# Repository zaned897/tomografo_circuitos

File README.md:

# tomografo_circuitos
todos los circuitos del tomografo fotoacustico

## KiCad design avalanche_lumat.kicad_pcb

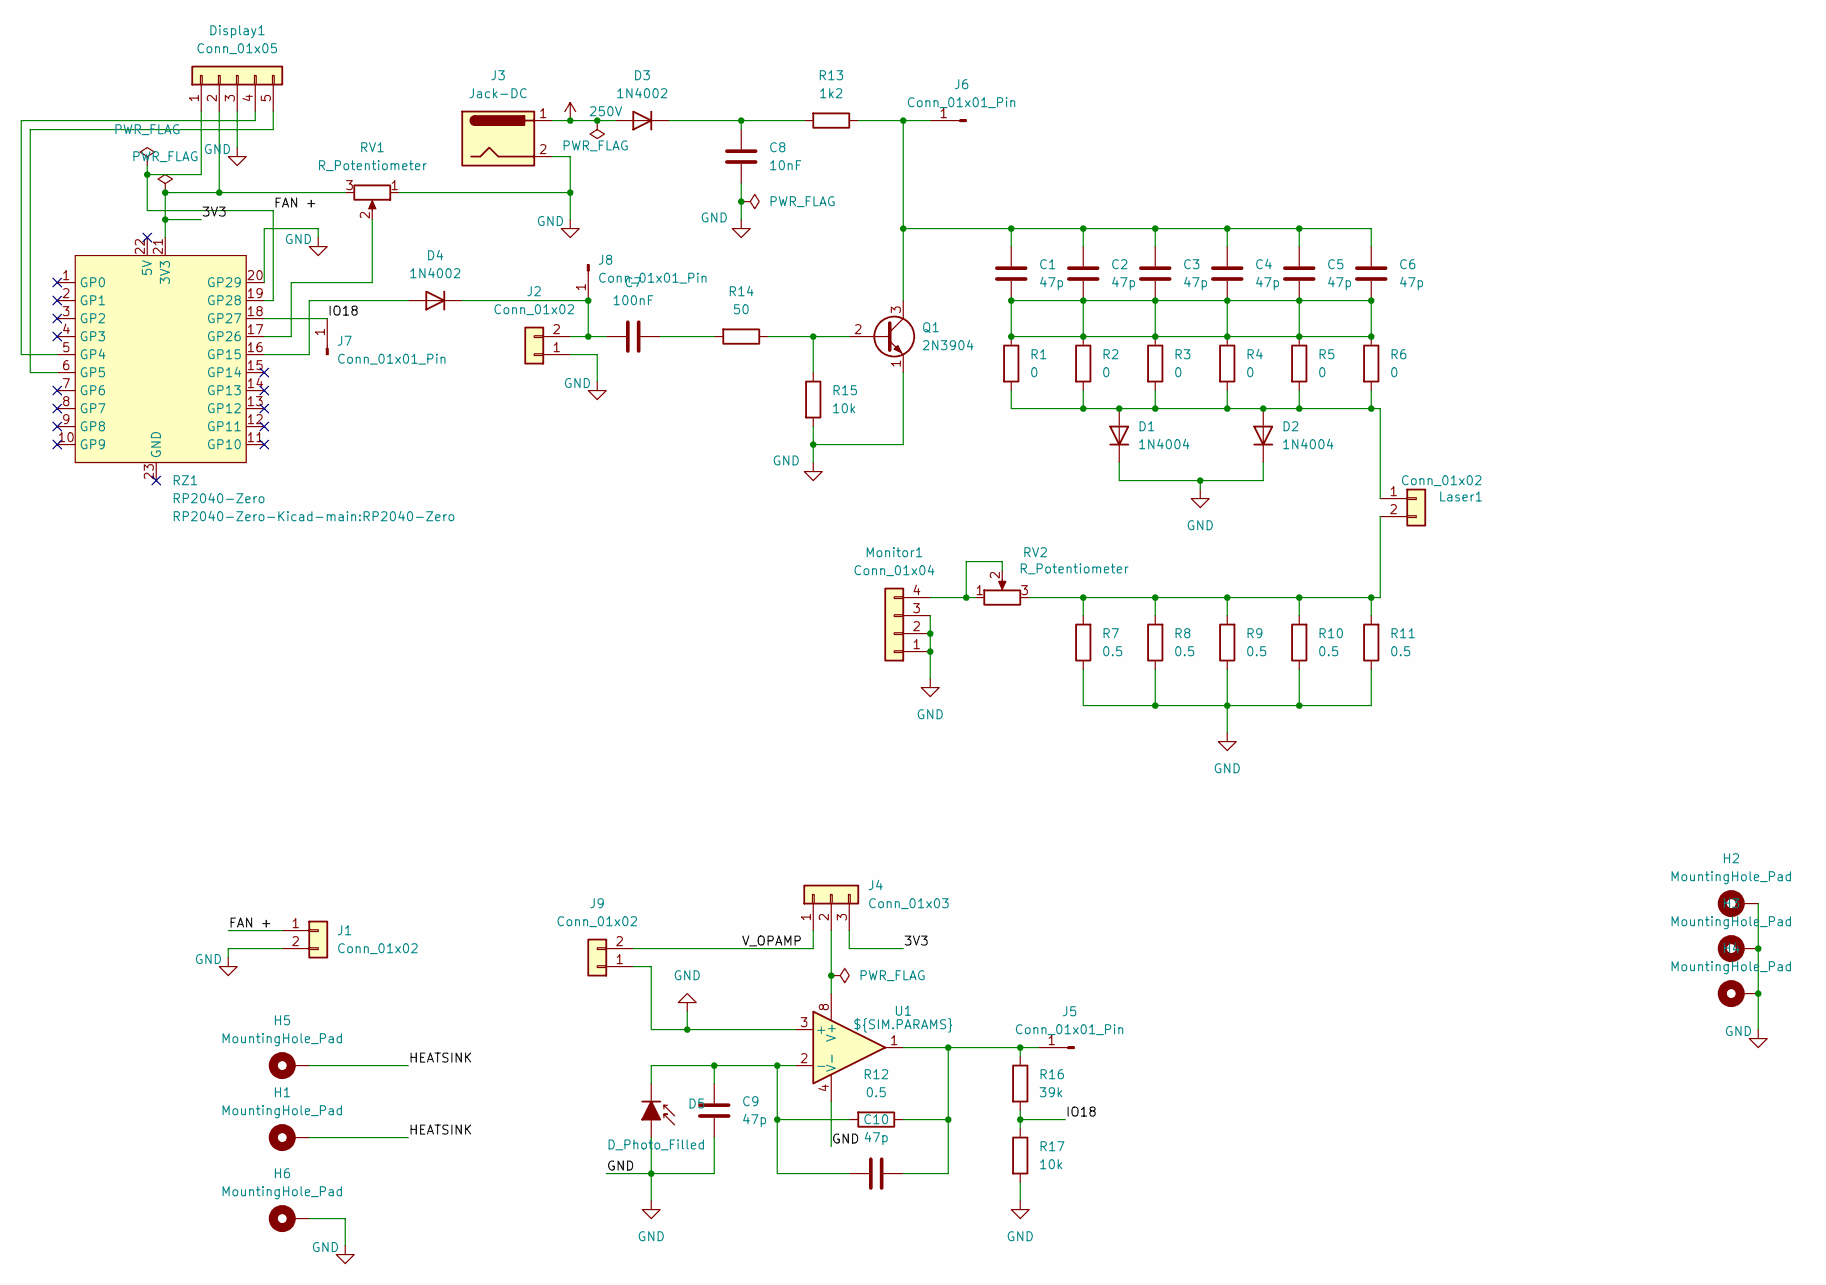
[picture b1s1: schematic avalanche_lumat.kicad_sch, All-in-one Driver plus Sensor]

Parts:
C1, C2, C3, C4, C5, C6, C9, C10: 47p; C_1206_3216Metric_Pad1.33x1.80mm_HandSolder
C7: 100nF; C_Disc_D4.7mm_W2.5mm_P5.00mm
C8: 10nF; C_Disc_D10.0mm_W2.5mm_P5.00mm
D1, D2: 1N4004; D_DO-41_SOD81_P10.16mm_Horizontal
D3, D4: 1N4002; D_DO-41_SOD81_P10.16mm_Horizontal
D5: D_Photo_Filled; TO-5-2_Window
Display1: Conn_01x05; PinSocket_1x05_P2.54mm_Vertical
H1, H5, H6: MountingHole_Pad; Mounting_Wuerth_WA-SMSI-M1.6_H2.5mm_ThreadDepth1.5mm_NoNPTH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
H2, H3, H4: MountingHole_Pad; MountingHole_3.2mm_M3_DIN965_Pad
J1: Conn_01x02; JST_PH_B2B-PH-K_1x02_P2.00mm_Vertical
J2, J9: Conn_01x02; PinHeader_1x02_P2.54mm_Vertical
J3: Jack-DC; BarrelJack_Horizontal
J4: Conn_01x03; PinHeader_1x03_P2.54mm_Vertical
J5, J6, J7, J8: Conn_01x01_Pin; TestPoint_Pad_D1.0mm
Laser1: Conn_01x02; TO-46-2_Window
Monitor1: Conn_01x04; PinHeader_1x04_P2.54mm_Vertical
Q1: 2N3904; TO-92_Inline
R1, R2, R3, R4, R5, R6: 0; R_1206_3216Metric_Pad1.30x1.75mm_HandSolder
R7, R8, R9, R10, R11, R12: 0.5; R_1206_3216Metric_Pad1.30x1.75mm_HandSolder
R13: 1k2; R_Axial_Power_L60.0mm_W14.0mm_P66.04mm
R14: 50; R_Axial_DIN0309_L9.0mm_D3.2mm_P12.70mm_Horizontal
R15: 10k; R_Axial_DIN0309_L9.0mm_D3.2mm_P12.70mm_Horizontal
R16: 39k; R_1206_3216Metric_Pad1.30x1.75mm_HandSolder
R17: 10k; R_1206_3216Metric_Pad1.30x1.75mm_HandSolder
RV1, RV2: R_Potentiometer; Potentiometer_Piher_PT-6-V_Vertical
RZ1: RP2040-Zero
U1: ${SIM.PARAMS}; DIP-8_W7.62mm

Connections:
250V: D3.2 (A), J3.1
/3V3: Display1.2, J4.3, RV1.3, RZ1.21 (3V3)
/FAN +: Display1.1, J1.1, RZ1.19 (GP28)
/HEATSINK: H1.1, H5.1
/IO18: J7.1, R16.2, R17.1, RZ1.18 (GP27)
/V_OPAMP: J4.1, J9.2
GND: C8.1, C9.2, D1.1 (K), D2.1 (K), D5.2 (A), Display1.3, H2.1, H3.1, H4.1, H6.1, J1.2, J2.1, J3.2, J9.1, Monitor1.1, Monitor1.2, Monitor1.3, Q1.1 (E), R7.1, R8.1, R9.1, R10.1, R11.1, R15.2, R17.2, RV1.1, RZ1.20 (GP29), U1.3 (+), U1.4 (V-)
unnamed: C1.2, C2.2, C3.2, C4.2, C5.2, C6.2, R1.1, R2.1, R3.1, R4.1, R5.1, R6.1
unnamed: C7.2, R14.2
unnamed: D1.2 (A), D2.2 (A), Laser1.1, R1.2, R2.2, R3.2, R4.2, R5.2, R6.2
unnamed: C8.2, D3.1 (K), R13.2
unnamed: D4.2 (A), RZ1.16 (GP15)
unnamed: C7.1, D4.1 (K), J2.2, J8.1
unnamed: C9.1, C10.1, D5.1 (K), R12.2, U1.2 (-)
unnamed: Display1.4, RZ1.5 (GP4)
unnamed: Display1.5, RZ1.6 (GP5)
unnamed: J4.2, U1.8 (V+)
unnamed: C10.2, J5.1, R12.1, R16.1, U1.1
unnamed: C1.1, C2.1, C3.1, C4.1, C5.1, C6.1, J6.1, Q1.3 (C), R13.1
unnamed: Laser1.2, R7.2, R8.2, R9.2, R10.2, R11.2, RV2.3
unnamed: Monitor1.4, RV2.1, RV2.2
unnamed: Q1.2 (B), R14.1, R15.1
unnamed: RV1.2, RZ1.17 (GP26)

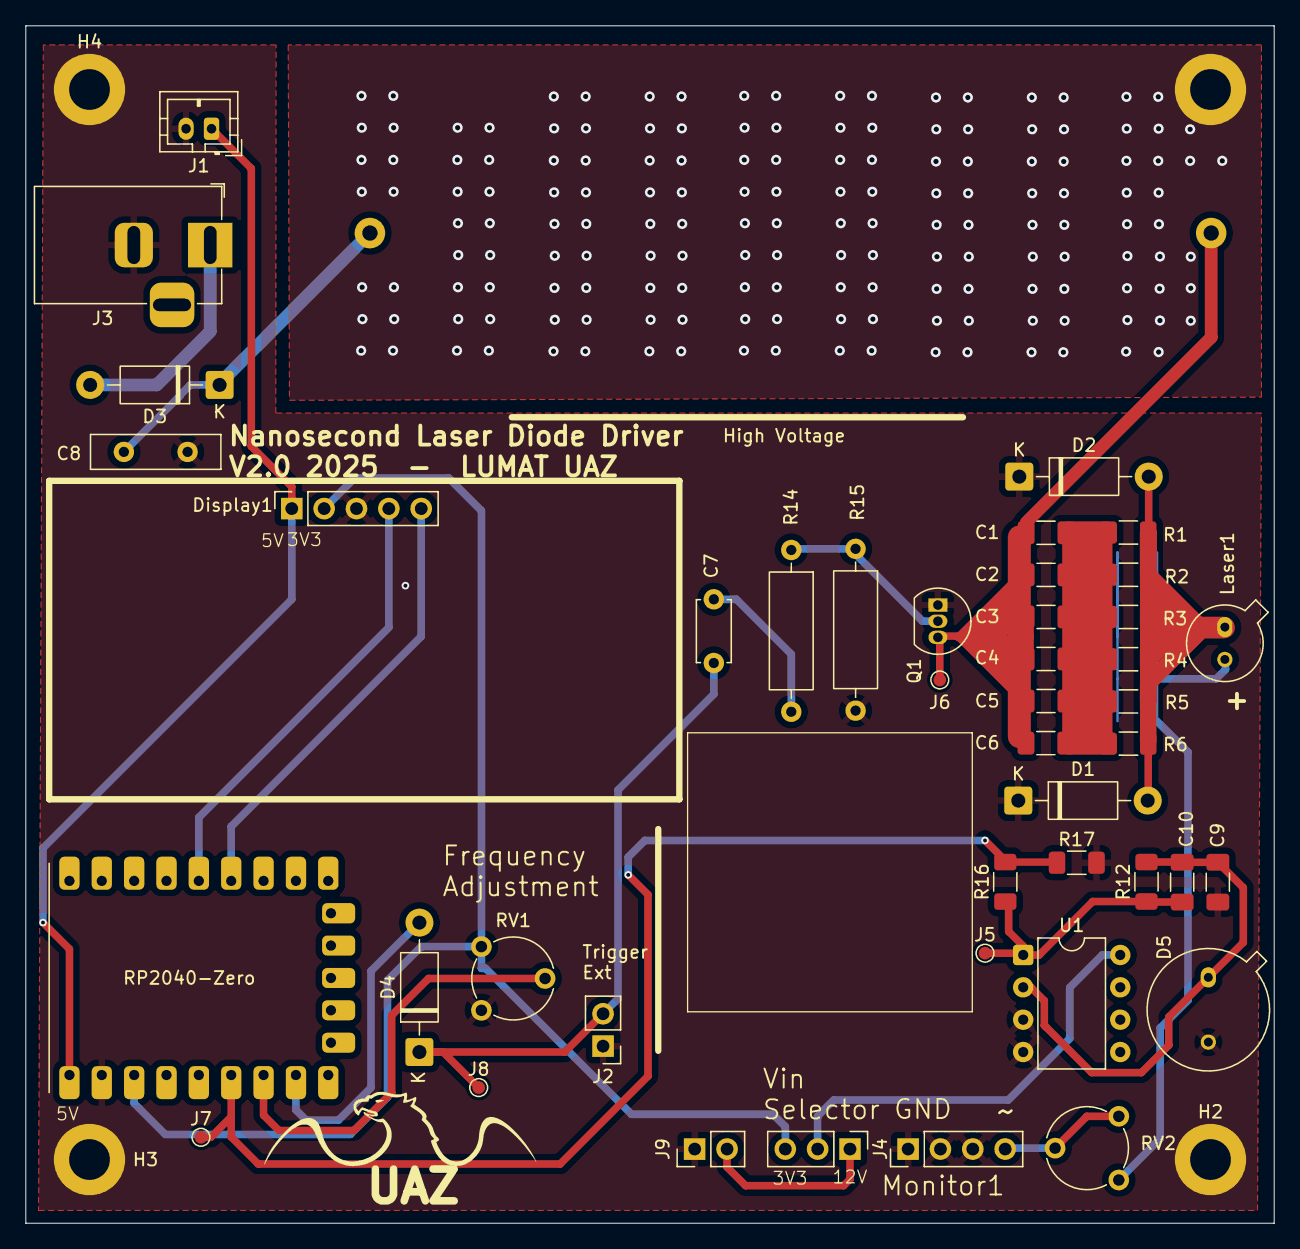
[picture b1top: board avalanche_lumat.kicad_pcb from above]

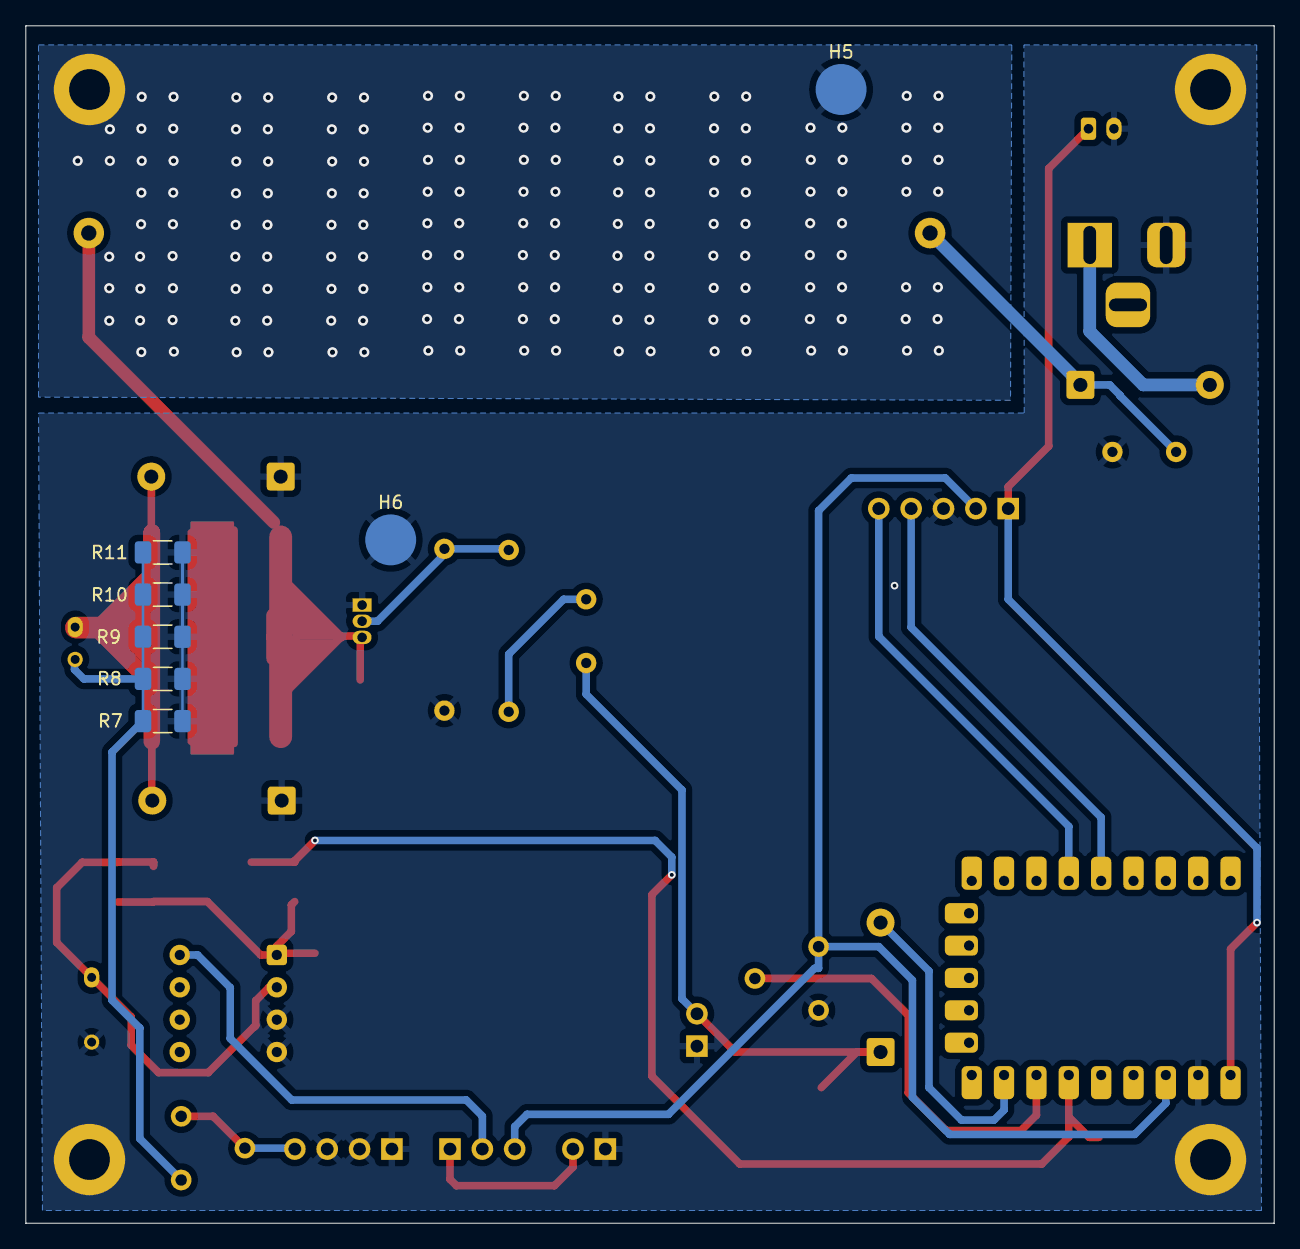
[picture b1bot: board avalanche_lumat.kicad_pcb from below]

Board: 2 copper layers, 98.0 x 94.0 mm, 55 parts (7 on the bottom side), 23 nets.

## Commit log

2026-01-29 feat: init commit
